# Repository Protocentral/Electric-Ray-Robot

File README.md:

Electric Ray Robot
======================

[  *Electric Ray Arduino-compatible robot (PC-0213)*](https://www.protocentral.com/robotics-kits/475-electric-ray-robot.html?search_query=electric+ray&results=3)

Electric Ray is a Ardino-Uno compatible, entry-level, low-cost complete robotic platform. It is simple enough to be used out-of-the-box for teaching and learning about robotics, electronics and Arduino programming. At the same time, it also allows one to add any number unlimited functions with the help of Arduino-compatible shields.

Specifications
---------------
* Atmega328 microcontroller with Optiboot bootloader (Arduino-Uno compatible)
* Arduino shield expansion headers
* Ultrasonic distance sensor
* 3x IR sensors
* OLED display
* Piezo buzzer
* FTDI USB-to-serial coverter
* TB6612FNG Motor Driver
* 2x 3V geared motors
* 2x wheels with rubber tyres
* 1100 mAH, 3.7V Li-Poly battery pack
* Clear acrylic sheet to cover the PCB

Repository Contents
-------------------
* **/Libraries** - Arduino library and example sketches.
* **/Hardware** - All Eagle design files (.brd, .sch)
* **/extras** - includes the datasheet

License Information
-------------------
This product is open source!

Please use, reuse, and modify these files as you see fit. Please maintain attribution to Protocentral and release anything derivative under the same license.

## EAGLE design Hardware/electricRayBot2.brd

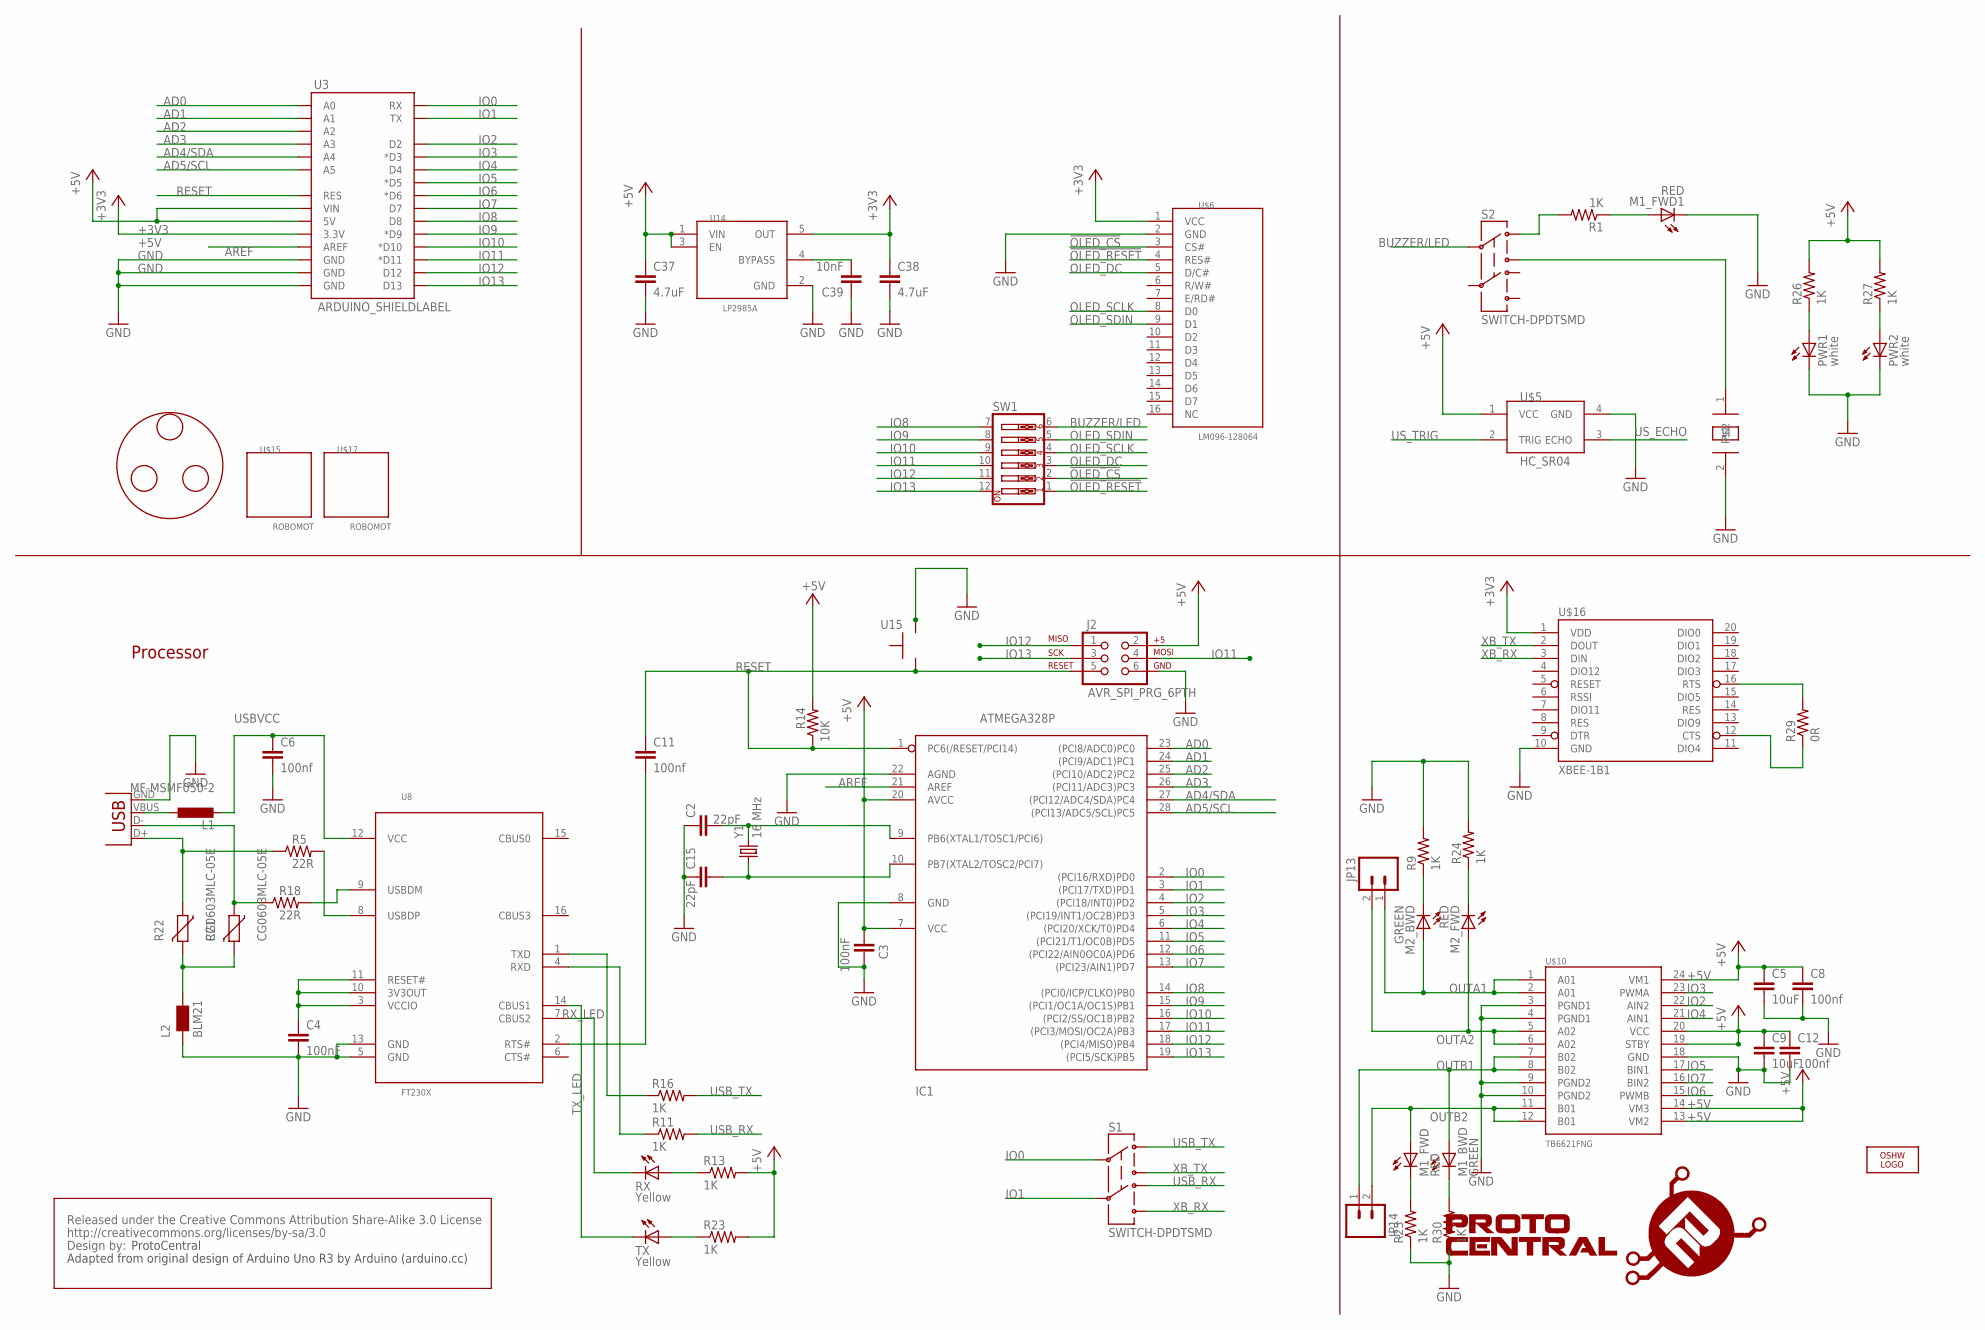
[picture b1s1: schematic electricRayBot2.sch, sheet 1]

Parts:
C2, C15: 22pF; C0402
C3, C4: 100nF; C0805
C5, C9: 10uF; C0805
C6, C8, C11, C12: 100nf; C0805
C37, C38: 4.7uF; C0805
C39: 10nF; C0805
IC1: ATMEGA328P; DIP28
J2: AVR_SPI_PRG_6PTH; 2X3
JP13, JP14: M023.5MM; SCREWTERMINAL-3.5MM-2
L1: MF-MSMF050-2; L1812
L2: BLM21; 0805
LOGO2: OSHW_LOGO_FILLX0350-NT; OSHW_FILLX350_NOTEXT
M1_BWD, M2_BWD: GREEN; CHIPLED_0603
M1_FWD, M1_FWD1, M2_FWD: RED; CHIPLED_0603
PWR1, PWR2: white; LED-0603
R1, R9, R11, R13, R16, R23, R24, R25, R26, R27, R30: 1K; R0805
R5, R18: 22R; R0805
R14: 10K; R0805
R21, R22: CG0603MLC-05E; CT/CN0603
R29: 0R; R0805
RX: Yellow; CHIPLED_0603
S1, S2: SWITCH-DPDTSMD; AYZ0202
SW1: SW_DIP-6; EDG-06
TX: Yellow; CHIPLED_0603
U3: ARDUINO_SHIELDLABEL; DUEMILANOVE_SHIELD
U8: FT230X; SSOP_16
U14: LP2985A; SOT23-5
U15: EVQQ2
U$1: CREATIVE_COMMONS
U$4: PS1740; PS02
U$5: HC_SR04; ULTRA
U$6: LM096-128064; LM096-128064(OLED)
U$10: TB6621FNG; SSOP24
U$15, U$17: ROBOMOT
U$16: XBEE-1B1; XBEE-1
U$18: PROTY-LOGO; LOGO-PROTY
U$20: MOTO
X1: USBPTH; USB-B-PTH
Y1: 16 MHz; HC49US

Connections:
!OLED_CS: SW1.2, U$6.3 (CS#)
!OLED_RESET: SW1.1, U$6.4 (RES#)
+3V3: C38.1, U3.3.3V, U14.5 (OUT), U$6.1 (VCC), U$16.1 (VDD)
+5V: C3.1, C5.1, C8.1, C9.1, C12.1, C37.1, IC1.7 (VCC), IC1.20 (AVCC), J2.2, R13.2, R14.2, R23.2, R26.2, R27.2, U3.5V, U3.VIN, U14.1 (VIN), U14.3 (EN), U$5.1 (VCC), U$10.13 (VM2), U$10.14 (VM3), U$10.19 (STBY), U$10.20 (VCC), U$10.24 (VM1); also elsewhere on the board
AD0: IC1.23 ((PCI8/ADC0)PC0), U3.A0; also elsewhere on the board
AD1: IC1.24 ((PCI9/ADC1)PC1), U3.A1; also elsewhere on the board
AD2: IC1.25 ((PCI10/ADC2)PC2), U3.A2; also elsewhere on the board
AD3: IC1.26 ((PCI11/ADC3)PC3), U3.A3; also elsewhere on the board
AD4/SDA: IC1.27 ((PCI12/ADC4/SDA)PC4), U3.A4; also elsewhere on the board
AD5/SCL: IC1.28 ((PCI13/ADC5/SCL)PC5), U3.A5; also elsewhere on the board
AREF: IC1.21 (AREF), U3.AREF
BUZZER: S2.3, U$4.1
BUZZER/LED: S2.2, SW1.6
GND: C2.1, C3.2, C4.2, C5.2, C6.2, C8.2, C9.2, C12.2, C15.1, C37.2, C38.2, C39.1, IC1.8 (GND), IC1.22 (AGND), J2.6, L2.1, M1_FWD1.C, PWR1.C, PWR2.C, R9.2, R24.2, R25.1, R30.1, U3.GND@0 (GND), U3.GND@1 (GND), U3.GND@2 (GND), U8.5 (GND), U8.13 (GND), U14.2 (GND), U15.P$3, U$4.2, U$5.4 (GND), U$6.2 (GND), U$10.3 (PGND1), U$10.4 (PGND1), U$10.9 (PGND2), U$10.10 (PGND2), U$10.18 (GND), U$16.10 (GND), X1.GND; also elsewhere on the board
IO0: IC1.2 ((PCI16/RXD)PD0), S1.2, U3.RX
IO1: IC1.3 ((PCI17/TXD)PD1), S1.5, U3.TX
IO2: IC1.4 ((PCI18/INT0)PD2), U3.D2, U$10.22 (AIN2)
IO3: IC1.5 ((PCI19/INT1/OC2B)PD3), U3.D3 (*D3), U$10.23 (PWMA)
IO4: IC1.6 ((PCI20/XCK/T0)PD4), U3.D4, U$10.21 (AIN1)
IO5: IC1.11 ((PCI21/T1/OC0B)PD5), U3.D5 (*D5), U$10.17 (BIN1)
IO6: IC1.12 ((PCI22/AIN0OC0A)PD6), U3.D6 (*D6), U$10.15 (PWMB)
IO7: IC1.13 ((PCI23/AIN1)PD7), U3.D7, U$10.16 (BIN2)
IO8: IC1.14 ((PCI0/ICP/CLKO)PB0), SW1.7, U3.D8
IO9: IC1.15 ((PCI1/OC1A/OC1S)PB1), SW1.8, U3.D9 (*D9)
IO10: IC1.16 ((PCI2/SS/OC1B)PB2), SW1.9, U3.D10 (*D10)
IO11: IC1.17 ((PCI3/MOSI/OC2A)PB3), J2.4, SW1.10, U3.D11 (*D11)
IO12: IC1.18 ((PCI4/MISO)PB4), J2.1, SW1.11, U3.D12
IO13: IC1.19 ((PCI5/SCK)PB5), J2.3, SW1.12, U3.D13
unnamed: PWR1.A, R26.1
unnamed: M1_FWD1.A, R1.1
unnamed: M2_BWD.C, R9.1
unnamed: PWR2.A, R27.1
unnamed: R18.2, U8.9 (USBDM)
unnamed: C4.1, U8.3 (VCCIO), U8.10 (3V3OUT), U8.11 (RESET#)
unnamed: R18.1, R21.1, X1.D-
unnamed: R5.2, U8.8 (USBDP)
unnamed: L1.1, X1.VBUS
unnamed: M1_FWD.C, R25.2
unnamed: M1_BWD.C, R30.2
unnamed: R29.2, U$16.16 (RTS)
unnamed: C39.2, U14.4 (BYPASS)
unnamed: R29.1, U$16.12 (CTS)
unnamed: M2_FWD.C, R24.1
unnamed: R1.2, S2.1
unnamed: R16.1, U8.1 (TXD)
unnamed: R11.1, U8.4 (RXD)
unnamed: R13.1, RX.A
unnamed: R23.1, TX.A
unnamed: C2.2, IC1.9 (PB6(XTAL1/TOSC1/PCI6)), Y1.2
unnamed: C15.2, IC1.10 (PB7(XTAL2/TOSC2/PCI7)), Y1.1
unnamed: C11.2, U8.2 (RTS#)
unnamed: L2.2, R21.2, R22.2
unnamed: R5.1, R22.1, X1.D+
OLED_DC: SW1.3, U$6.5 (D/C#)
OLED_SCLK: SW1.4, U$6.8 (D0)
OLED_SDIN: SW1.5, U$6.9 (D1)
OUTA1: JP13.1, M2_BWD.A, U$10.1 (A01), U$10.2 (A01)
OUTA2: JP13.2, M2_FWD.A, U$10.5 (A02), U$10.6 (A02)
OUTB1: JP14.1, M1_BWD.A, U$10.7 (B02), U$10.8 (B02)
OUTB2: JP14.2, M1_FWD.A, U$10.11 (B01), U$10.12 (B01)
RESET: C11.1, IC1.1 (PC6(/RESET/PCI14)), J2.5, R14.1, U3.RES, U15.P$1
RX_LED: RX.C, U8.7 (CBUS2)
TX_LED: TX.C, U8.14 (CBUS1)
USBVCC: C6.1, L1.2, U8.12 (VCC); also elsewhere on the board
USB_RX: R11.2, S1.4
USB_TX: R16.2, S1.1
US_ECHO: U$5.3 (ECHO); also elsewhere on the board
US_TRIG: U$5.2 (TRIG); also elsewhere on the board
XB_RX: S1.6, U$16.3 (DIN)
XB_TX: S1.3, U$16.2 (DOUT)

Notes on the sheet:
Processor
ProtoCentral
Adapted from original design of Arduino Uno R3 by Arduino (arduino.cc)

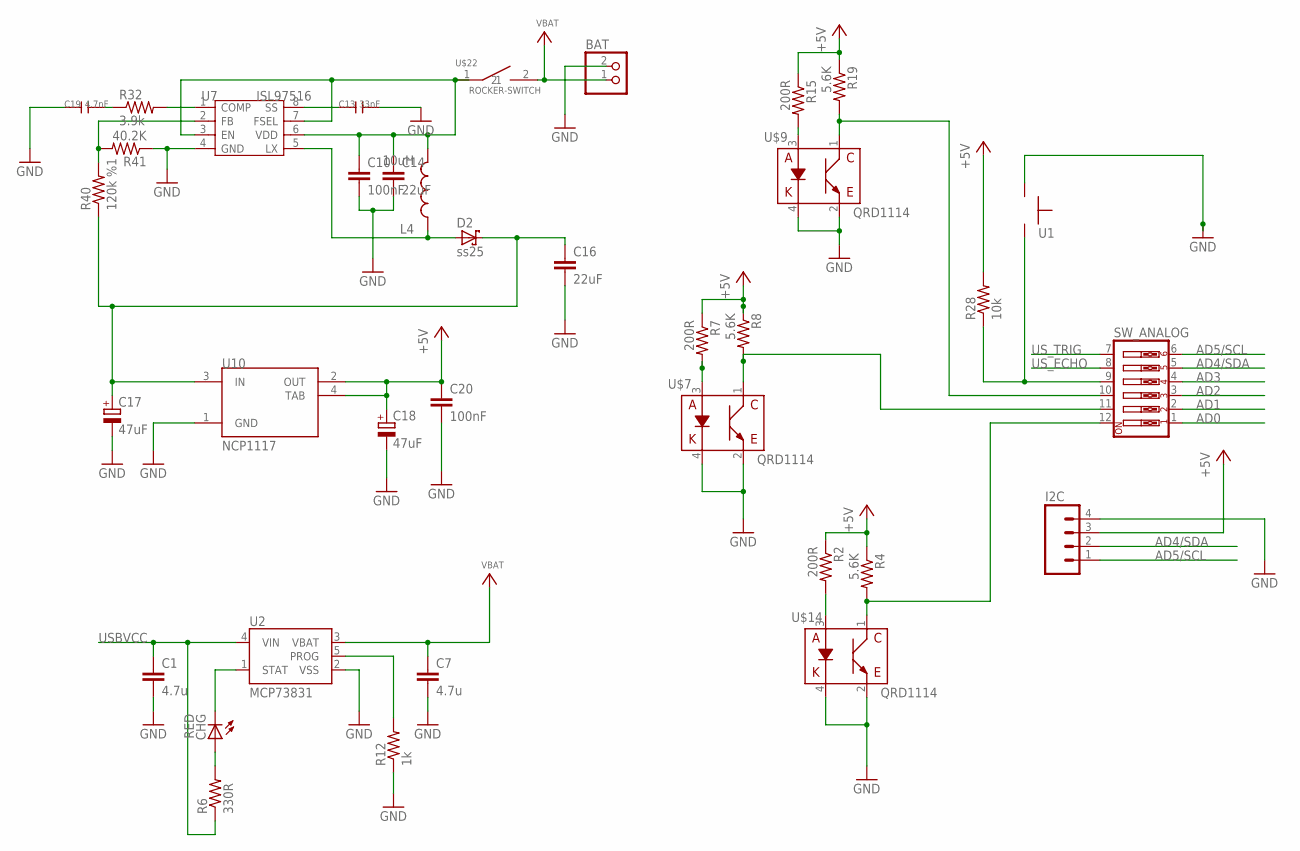
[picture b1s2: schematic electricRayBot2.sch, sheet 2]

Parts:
BAT: JST_2PIN-THM; JST-PH-2-THM
C1, C7: 4.7u; C0805
C10: 100nF; C0805
C13: 33nF; C0603
C14, C16: 22uF; C1206
C17, C18: 47uF; PANASONIC_D
C19: 4.7nF; C0603
C20: 100nF; C0402
CHG: RED; CHIPLED_0603
D2: ss25; SMB
I2C: M04POLAR_LOCK; MOLEX-1X4_LOCK
L4: 10uH; CDRH8D43
R2, R7, R15: 200R; R0805
R4, R8, R19: 5.6K; R0805
R6: 330R; R0805
R12: 1k; R0805
R28: 10k; R0805
R32: 3.9k; R0805
R40: 120k %1; R0805
R41: 40.2K; R0805
SW_ANALOG: SW_DIP-6; EDG-06
U1: EVQQ2
U2: MCP73831; SOT23-5
U7: ISL97516; MSOP8
U10: NCP1117; SOT223
U$7, U$9, U$14: QRD1114
U$22: ROCKER-SWITCH; SPST(RIGHT-ANGLE)

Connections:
+5V: C18.+, C20.1, I2C.3, R2.1, R4.1, R7.1, R8.1, R15.1, R19.1, R28.2, U10.2 (OUT), U10.4 (TAB); also elsewhere on the board
AD0: SW_ANALOG.1; also elsewhere on the board
AD1: SW_ANALOG.2; also elsewhere on the board
AD2: SW_ANALOG.3; also elsewhere on the board
AD3: SW_ANALOG.4; also elsewhere on the board
AD4/SDA: I2C.2, SW_ANALOG.5; also elsewhere on the board
AD5/SCL: I2C.1, SW_ANALOG.6; also elsewhere on the board
GND: BAT.2 (1), C1.2, C7.2, C10.2, C13.2, C14.2, C16.2, C17.-, C18.-, C19.1, C20.2, I2C.4, R12.1, R41.1, U1.P$1, U2.2 (VSS), U7.4 (GND), U10.1 (GND), U$7.2 (C), U$7.4 (K), U$9.2 (C), U$9.4 (K), U$14.2 (C), U$14.4 (K); also elsewhere on the board
IR1: R15.2, U$9.3 (A)
IR4: R7.2, U$7.3 (A)
IR5: R2.2, U$14.3 (A)
unnamed: CHG.C, U2.1 (STAT)
unnamed: CHG.A, R6.2
unnamed: R28.1, SW_ANALOG.9, U1.P$3
unnamed: C16.1, C17.+, D2.C, R40.1, U10.3 (IN)
unnamed: C13.1, U7.8 (SS)
unnamed: D2.A, L4.P$1 (1), U7.5 (LX)
unnamed: R12.2, U2.5 (PROG)
unnamed: R32.2, U7.1 (COMP)
unnamed: C19.2, R32.1
unnamed: R4.2, SW_ANALOG.12, U$14.1 (E)
unnamed: R8.2, SW_ANALOG.11, U$7.1 (E)
unnamed: R40.2, R41.2, U7.2 (FB)
unnamed: R19.2, SW_ANALOG.10, U$9.1 (E)
USBVCC: C1.1, R6.1, U2.4 (VIN); also elsewhere on the board
US_ECHO: SW_ANALOG.8; also elsewhere on the board
US_TRIG: SW_ANALOG.7; also elsewhere on the board
VBAT: BAT.1 (2), C7.1, U2.3 (VBAT), U$22.2
VDD: C10.1, C14.1, L4.P$2 (2), U7.3 (EN), U7.6 (VDD), U7.7 (FSEL), U$22.1

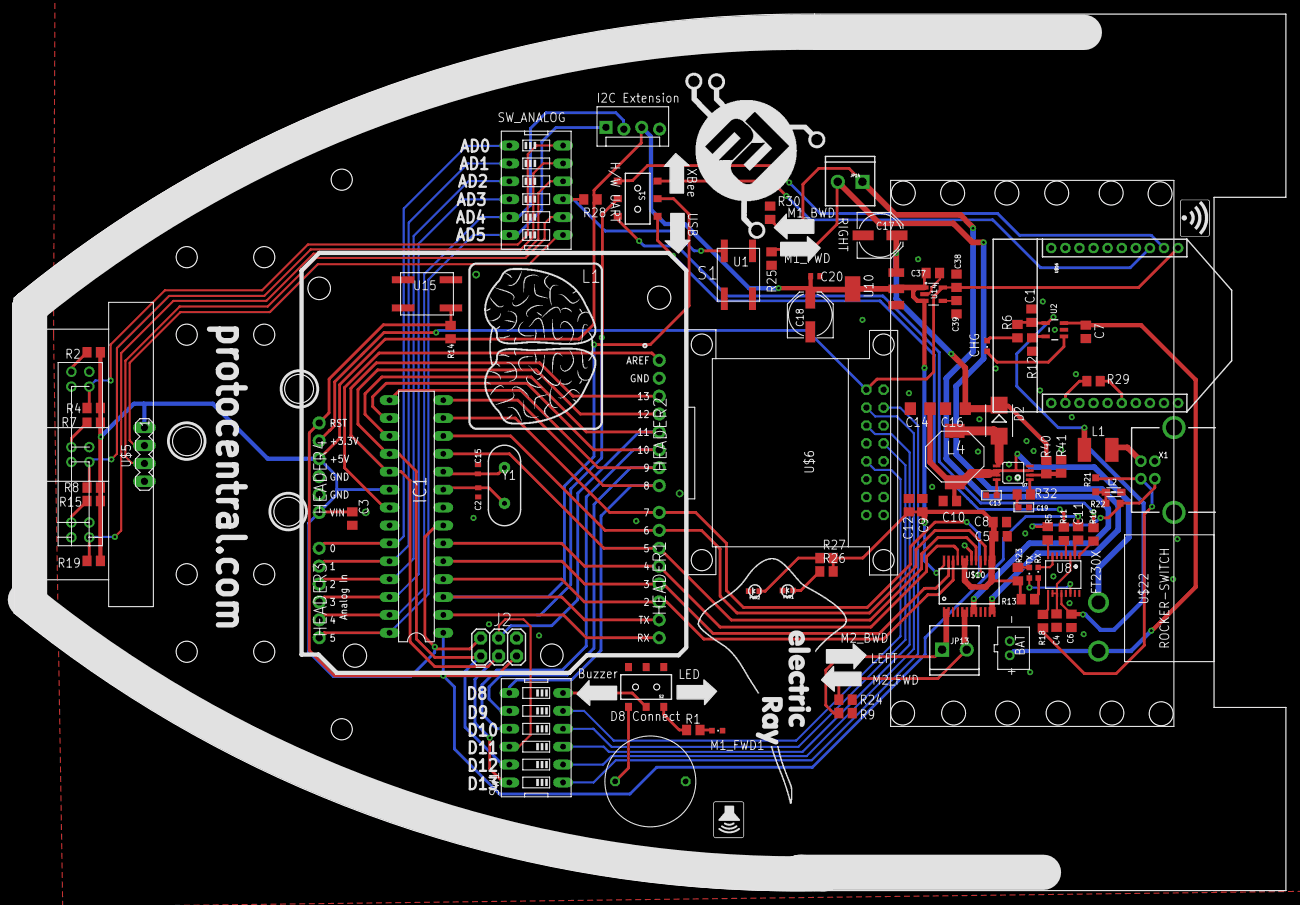
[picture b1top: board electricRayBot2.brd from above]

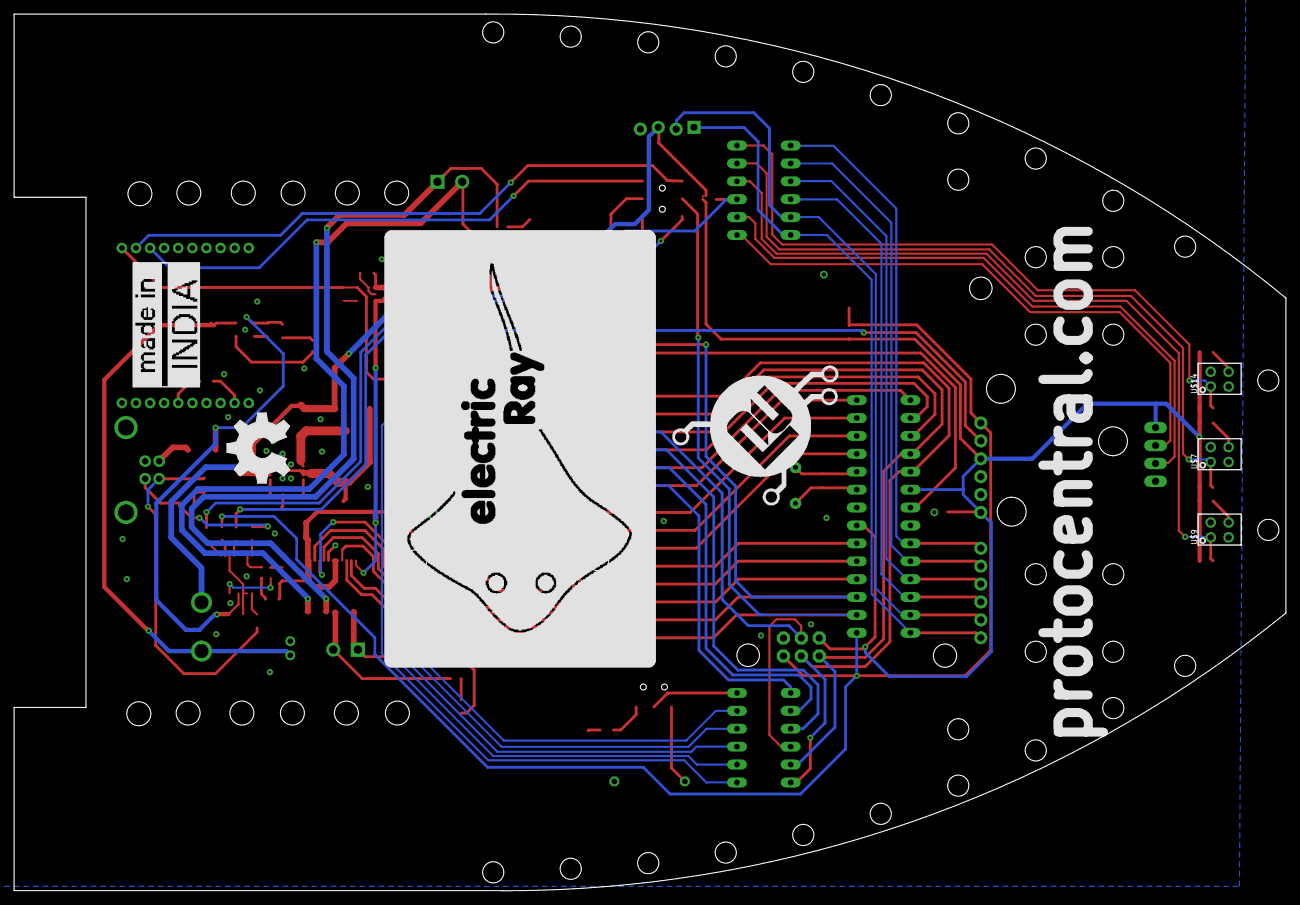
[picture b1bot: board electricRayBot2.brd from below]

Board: 4 copper layers, 180.5 x 124.4 mm, 109 parts (8 on the bottom side), 88 nets.

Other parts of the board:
U$2: MADEININDIA
U$3: BMP-SPEAKER
U$11: BMP-ELECTRICRAY
U$13, U$36: PROTY-LOGO-LARGE
U$19: BMP-WIRELESS
U$21: BMP-BRAIN
U$37: LOGO-ELECTRICRAY

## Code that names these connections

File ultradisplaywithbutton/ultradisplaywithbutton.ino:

#include <Wire.h>
#include <Adafruit_GFX.h>
#include <Adafruit_SSD1306.h>

#define OLED_DC 11
#define OLED_CS 12
#define OLED_CLK 10
#define OLED_MOSI 9
#define OLED_RESET 13
Adafruit_SSD1306 display(OLED_MOSI, OLED_CLK, OLED_DC, OLED_RESET, OLED_CS);

#define NUMFLAKES 10
#define XPOS 0
#define YPOS 1
#define DELTAY 2

#define trigPin A5
#define echoPin A4

#define buttonpin A3

#define LOGO16_GLCD_HEIGHT 16 
#define LOGO16_GLCD_WIDTH  16 
static unsigned char PROGMEM logo16_glcd_bmp[] =
{ B00000000, B11000000,
  B00000001, B11000000,
  B00000001, B11000000,
  B00000011, B11100000,
  B11110011, B11100000,
  B11111110, B11111000,
  B01111110, B11111111,
  B00110011, B10011111,
  B00011111, B11111100,
  B00001101, B01110000,
  B00011011, B10100000,
  B00111111, B11100000,
  B00111111, B11110000,
  B01111100, B11110000,
  B01110000, B01110000,
  B00000000, B00110000 };

#if (SSD1306_LCDHEIGHT != 64)
#error("Height incorrect, please fix Adafruit_SSD1306.h!");
#endif

void setup()   {                
  Serial.begin(9600);
  
  pinMode(trigPin, OUTPUT);
  pinMode(echoPin, INPUT);
  
  pinMode(buttonpin, INPUT);
  
  // by default, we'll generate the high voltage from the 3.3v line internally! (neat!)
  display.begin(SSD1306_SWITCHCAPVCC);
  // init done
  
  display.display(); // show splashscreen
  delay(2000);
  display.clearDisplay();   // clears the screen and buffer

 
}


void loop() {
  
  int button = digitalRead(buttonpin);
  if(button == HIGH)
  {
  distancedisplay();
  //delay(2000);
  display.clearDisplay();
  }
  else
  {
    buttonstate();
    delay(2000);
    display.clearDisplay();
  }
}


void testdrawbitmap(const uint8_t *bitmap, uint8_t w, uint8_t h) {
  uint8_t icons[NUMFLAKES][3];
  srandom(666);     // whatever seed
 
  // initialize
  for (uint8_t f=0; f< NUMFLAKES; f++) {
    icons[f][XPOS] = random() % display.width();
    icons[f][YPOS] = 0;
    icons[f][DELTAY] = random() % 5 + 1;
    
    Serial.print("x: ");
    Serial.print(icons[f][XPOS], DEC);
    Serial.print(" y: ");
    Serial.print(icons[f][YPOS], DEC);
    Serial.print(" dy: ");
    Serial.println(icons[f][DELTAY], DEC);
  }

  while (1) {
    // draw each icon
    for (uint8_t f=0; f< NUMFLAKES; f++) {
      display.drawBitmap(icons[f][XPOS], icons[f][YPOS], logo16_glcd_bmp, w, h, WHITE);
    }
    display.display();
    delay(200);
    
    // then erase it + move it
    for (uint8_t f=0; f< NUMFLAKES; f++) {
      display.drawBitmap(icons[f][XPOS], icons[f][YPOS],  logo16_glcd_bmp, w, h, BLACK);
      // move it
      icons[f][YPOS] += icons[f][DELTAY];
      // if its gone, reinit
      if (icons[f][YPOS] > display.height()) {
	icons[f][XPOS] = random() % display.width();
	icons[f][YPOS] = 0;
	icons[f][DELTAY] = random() % 5 + 1;
      }
    }
   }
}

void distancedisplay(void) {
   long duration, distance;
  digitalWrite(trigPin, LOW);  // Added this line
  delayMicroseconds(2); // Added this line
  digitalWrite(trigPin, HIGH);
  //  delayMicroseconds(1000); - Removed this line
  delayMicroseconds(10); // Added this line
  digitalWrite(trigPin, LOW);
  duration = pulseIn(echoPin, HIGH);
  distance = (duration/2) / 29.1;

  if (distance >= 200 || distance <= 0){
     display.setTextSize(2);
  display.setTextColor(WHITE);
  display.setCursor(0,0);
  display.clearDisplay();
  display.println("Out of range");
  display.display();
    
  }
  else {
     display.setTextSize(2);
  display.setTextColor(WHITE);
  display.setCursor(0,0);
  display.clearDisplay();
    display.print(distance);
    display.println(" cm");
    display.display();
  }
}

void buttonstate(void)
{
  display.setTextSize(2);
  display.setTextColor(WHITE);
  display.setCursor(0,0);
  display.clearDisplay();
  display.println("Switch is off");
  display.display();
}

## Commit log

2016-01-21 example sketch
2016-01-21 Design file
2016-01-21 Arduino Sketch

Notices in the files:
parts and their libraries:
SparkFun: Released under the Creative Commons Attribution Share-Alike 3.0 License
SparkFun: http://creativecommons.org/licenses/by-sa/3.0
